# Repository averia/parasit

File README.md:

# % parasit
16 digit for 7 segment display

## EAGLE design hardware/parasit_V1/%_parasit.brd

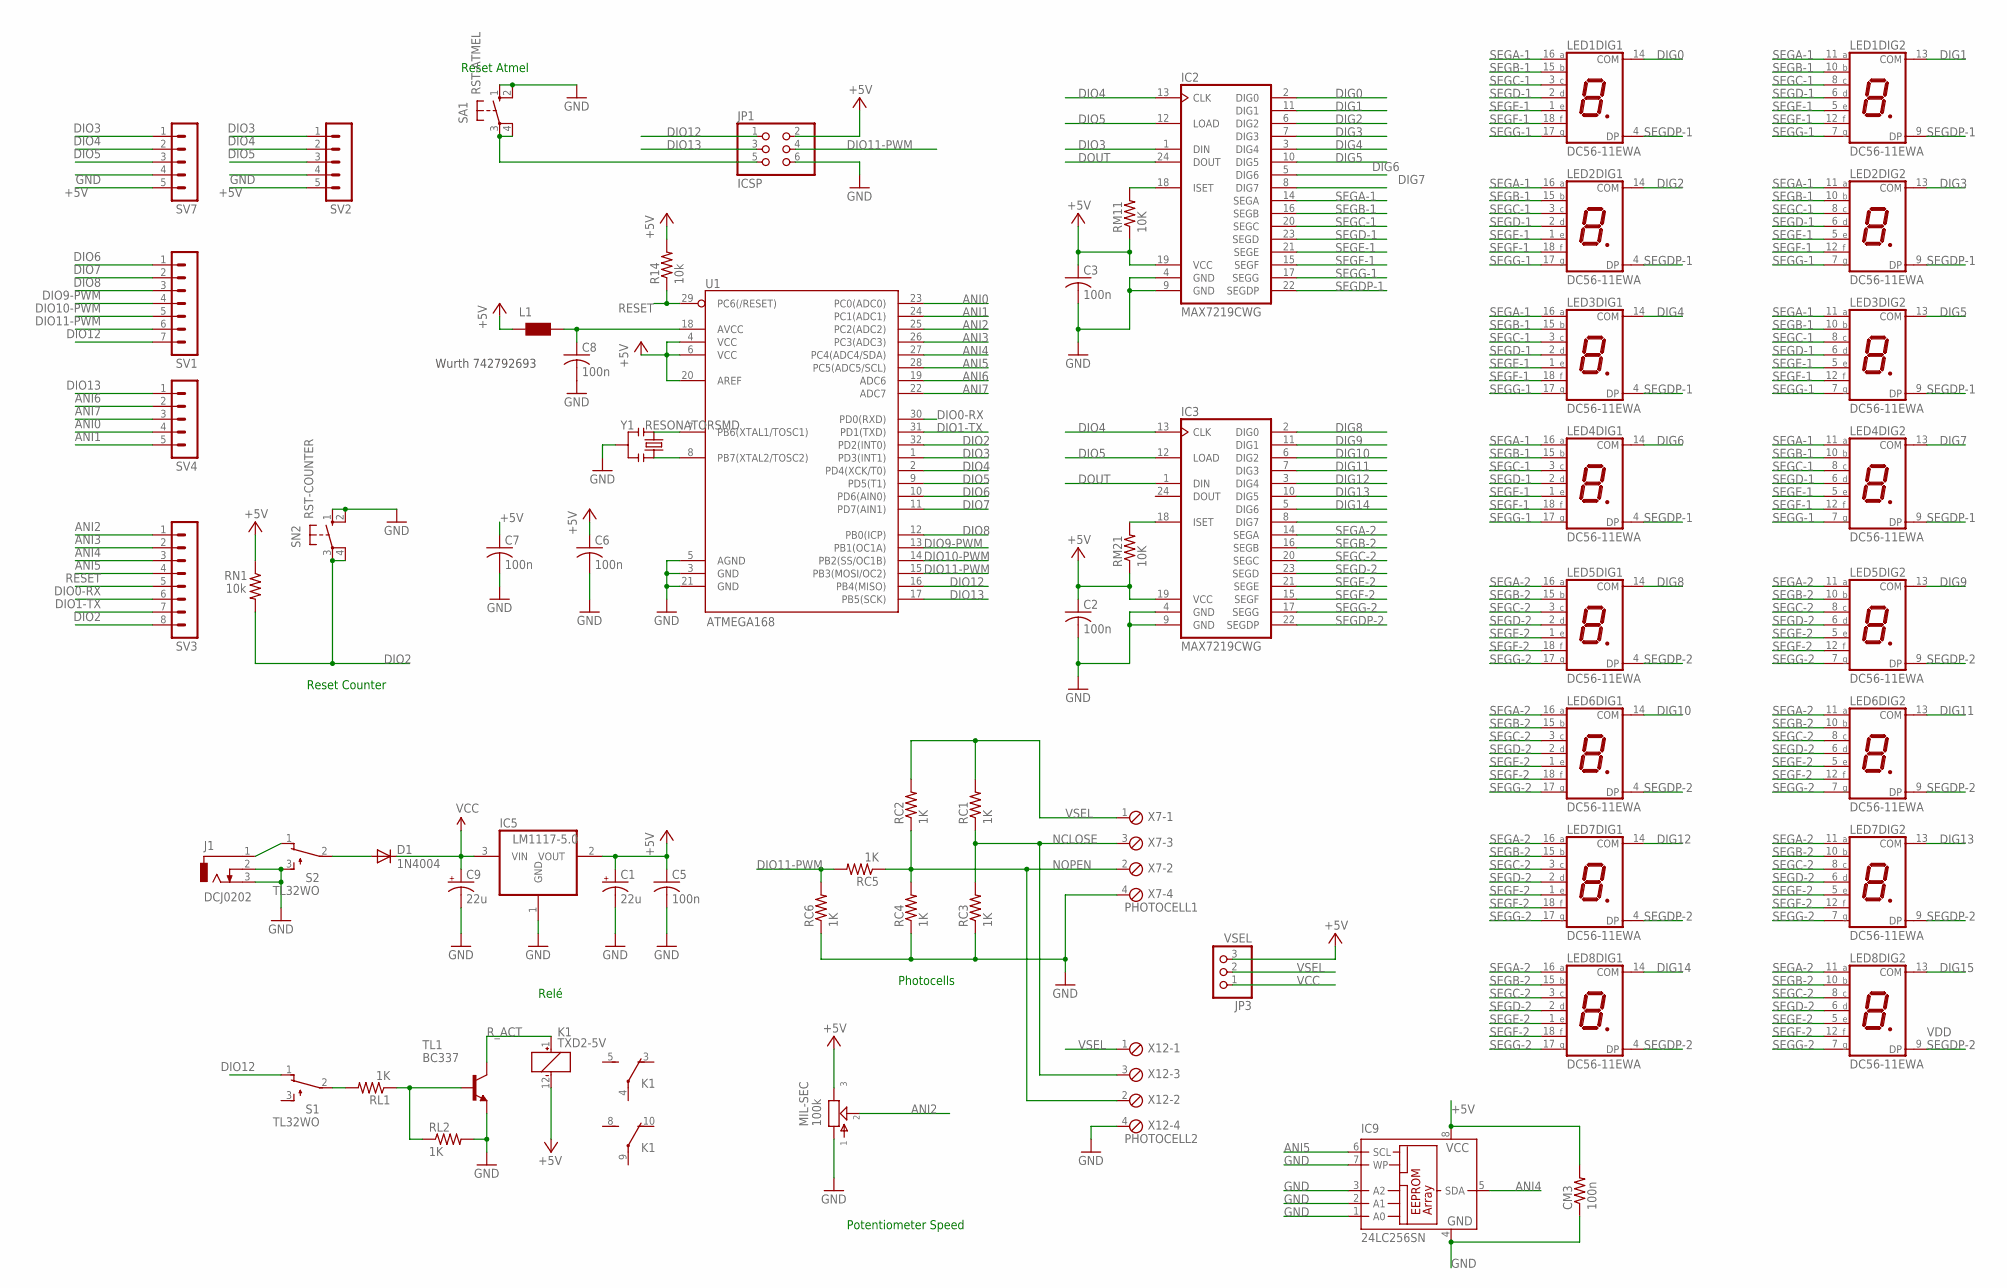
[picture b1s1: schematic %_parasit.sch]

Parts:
C1, C9: 22u; PANASONIC_C
C2, C3, C5, C6, C7, C8: 100n; C0603
CM3: 100n; R0603
D1: 1N4004; DO41-10
IC2, IC3: MAX7219CWG; SO24W
IC5: LM1117-5.0; SOT223
IC9: 24LC256SN; SO-08
J1: DCJ0202
JP1: ICSP; 2X03
JP3: VSEL; 1X03
K1: TXD2-5V; TXD2
L1: WE-CBF_0603; 0603
LED1, LED2, LED3, LED4, LED5, LED6, LED7, LED8: DC56-11EWA; DA56
MIL-SEC: 100k; 16MM-PCB-BRACKETS@1
R14: 10k; R0603
RC1, RC2, RC3, RC4, RC5, RC6: 1K; R0603
RL1, RL2: 1K; R0603
RM11, RM21: 10K; R0603
RN1: 10k; R0603
S1, S2: TL32WO; TL3XWO
SA1: RST-ATMEL; B3F-10XX
SN2: RST-COUNTER; B3F-10XX
SV1: MA07-1
SV2, SV4, SV7: MA05-1
SV3: MA08-1
TL1: BC337; TO92
U1: ATMEGA168; TQFP32-08
X7: PHOTOCELL1; 4POL254
X12: PHOTOCELL2; 4POL254
Y1: RESONATORSMD; RESONATOR-SMD

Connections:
+5V: C1.+, C2.1, C3.1, C5.1, C6.1, C7.1, CM3.2, IC2.19 (VCC), IC3.19 (VCC), IC5.2 (VOUT), IC9.8 (VCC), JP1.2, JP3.3, K1.12 (-), L1.1, MIL-SEC.3, R14.2, RM11.1, RM21.1, RN1.1, SV2.5, SV7.5, U1.4 (VCC), U1.6 (VCC), U1.20 (AREF)
ANI0: SV4.4, U1.23 (PC0(ADC0))
ANI1: SV4.5, U1.24 (PC1(ADC1))
ANI2: MIL-SEC.2, SV3.1, U1.25 (PC2(ADC2))
ANI3: SV3.2, U1.26 (PC3(ADC3))
ANI4: IC9.5 (SDA), SV3.3, U1.27 (PC4(ADC4/SDA))
ANI5: IC9.6 (SCL), SV3.4, U1.28 (PC5(ADC5/SCL))
ANI6: SV4.2, U1.19 (ADC6)
ANI7: SV4.3, U1.22 (ADC7)
DIG0: IC2.2 (DIG0), LED1.14 (COM)
DIG1: IC2.11 (DIG1), LED1.13 (COM)
DIG2: IC2.6 (DIG2), LED2.14 (COM)
DIG3: IC2.7 (DIG3), LED2.13 (COM)
DIG4: IC2.3 (DIG4), LED3.14 (COM)
DIG5: IC2.10 (DIG5), LED3.13 (COM)
DIG6: IC2.5 (DIG6), LED4.14 (COM)
DIG7: IC2.8 (DIG7), LED4.13 (COM)
DIG8: IC3.2 (DIG0), LED5.14 (COM)
DIG9: IC3.11 (DIG1), LED5.13 (COM)
DIG10: IC3.6 (DIG2), LED6.14 (COM)
DIG11: IC3.7 (DIG3), LED6.13 (COM)
DIG12: IC3.3 (DIG4), LED7.14 (COM)
DIG13: IC3.10 (DIG5), LED7.13 (COM)
DIG14: IC3.5 (DIG6), LED8.14 (COM)
DIG15: IC3.8 (DIG7), LED8.13 (COM)
DIO0-RX: SV3.6, U1.30 (PD0(RXD))
DIO1-TX: SV3.7, U1.31 (PD1(TXD))
DIO2: RN1.2, SN2.3, SN2.4 (P1), SV3.8, U1.32 (PD2(INT0))
DIO3: IC2.1 (DIN), SV2.1, SV7.1, U1.1 (PD3(INT1))
DIO4: IC2.13 (CLK), IC3.13 (CLK), SV2.2, SV7.2, U1.2 (PD4(XCK/T0))
DIO5: IC2.12 (LOAD), IC3.12 (LOAD), SV2.3, SV7.3, U1.9 (PD5(T1))
DIO6: SV1.1, U1.10 (PD6(AIN0))
DIO7: SV1.2, U1.11 (PD7(AIN1))
DIO8: SV1.3, U1.12 (PB0(ICP))
DIO9-PWM: SV1.4, U1.13 (PB1(OC1A))
DIO10-PWM: SV1.5, U1.14 (PB2(SS/OC1B))
DIO11-PWM: JP1.4, RC5.2, RC6.2, SV1.6, U1.15 (PB3(MOSI/OC2))
DIO12: JP1.1, S1.1 (O), SV1.7, U1.16 (PB4(MISO))
DIO13: JP1.3, SV4.1, U1.17 (PB5(SCK))
DOUT: IC2.24 (DOUT), IC3.1 (DIN)
GND: C1.-, C2.2, C3.2, C5.2, C6.2, C7.2, C8.2, C9.-, CM3.1, IC2.4 (GND), IC2.9 (GND), IC3.4 (GND), IC3.9 (GND), IC5.1 (GND), IC9.1 (A0), IC9.2 (A1), IC9.3 (A2), IC9.4 (GND), IC9.7 (WP), J1.2, J1.3, JP1.6, MIL-SEC.1, RC3.1, RC4.1, RC6.1, RL2.2, S2.3 (S), SA1.1 (S), SA1.2 (S1), SN2.1 (S), SN2.2 (S1), SV2.4, SV7.4, TL1.1 (E), U1.3 (GND), U1.5 (AGND), U1.21 (GND), X7.4, X12.4, Y1.2
unnamed: J1.1, S2.1 (O)
unnamed: D1.A, S2.2
unnamed: RL1.2, S1.2
unnamed: RL1.1, RL2.1, TL1.2 (B)
unnamed: U1.7 (PB6(XTAL1/TOSC1)), Y1.1
unnamed: IC2.18 (ISET), RM11.2
unnamed: IC3.18 (ISET), RM21.2
unnamed: U1.8 (PB7(XTAL2/TOSC2)), Y1.3
unnamed: C8.1, L1.2, U1.18 (AVCC)
NCLOSE: RC1.1, RC3.2, X7.3, X12.3
NOPEN: RC2.1, RC4.2, RC5.1, X7.2, X12.2
RESET: JP1.5, R14.1, SA1.3, SA1.4 (P1), SV3.5, U1.29 (PC6(/RESET))
R_ACT: K1.1 (+), TL1.3 (C)
SEGA-1: IC2.14 (SEGA), LED1.11 (A), LED1.16 (A), LED2.11 (A), LED2.16 (A), LED3.11 (A), LED3.16 (A), LED4.11 (A), LED4.16 (A)
SEGA-2: IC3.14 (SEGA), LED5.11 (A), LED5.16 (A), LED6.11 (A), LED6.16 (A), LED7.11 (A), LED7.16 (A), LED8.11 (A), LED8.16 (A)
SEGB-1: IC2.16 (SEGB), LED1.10 (B), LED1.15 (B), LED2.10 (B), LED2.15 (B), LED3.10 (B), LED3.15 (B), LED4.10 (B), LED4.15 (B)
SEGB-2: IC3.16 (SEGB), LED5.10 (B), LED5.15 (B), LED6.10 (B), LED6.15 (B), LED7.10 (B), LED7.15 (B), LED8.10 (B), LED8.15 (B)
SEGC-1: IC2.20 (SEGC), LED1.3 (C), LED1.8 (C), LED2.3 (C), LED2.8 (C), LED3.3 (C), LED3.8 (C), LED4.3 (C), LED4.8 (C)
SEGC-2: IC3.20 (SEGC), LED5.3 (C), LED5.8 (C), LED6.3 (C), LED6.8 (C), LED7.3 (C), LED7.8 (C), LED8.3 (C), LED8.8 (C)
SEGD-1: IC2.23 (SEGD), LED1.2 (D), LED1.6 (D), LED2.2 (D), LED2.6 (D), LED3.2 (D), LED3.6 (D), LED4.2 (D), LED4.6 (D)
SEGD-2: IC3.23 (SEGD), LED5.2 (D), LED5.6 (D), LED6.2 (D), LED6.6 (D), LED7.2 (D), LED7.6 (D), LED8.2 (D), LED8.6 (D)
SEGDP-1: IC2.22 (SEGDP), LED1.4 (DP), LED1.9 (DP), LED2.4 (DP), LED2.9 (DP), LED3.4 (DP), LED3.9 (DP), LED4.4 (DP), LED4.9 (DP)
SEGDP-2: IC3.22 (SEGDP), LED5.4 (DP), LED5.9 (DP), LED6.4 (DP), LED6.9 (DP), LED7.4 (DP), LED7.9 (DP), LED8.4 (DP), LED8.9 (DP)
SEGE-1: IC2.21 (SEGE), LED1.1 (E), LED1.5 (E), LED2.1 (E), LED2.5 (E), LED3.1 (E), LED3.5 (E), LED4.1 (E), LED4.5 (E)
SEGE-2: IC3.21 (SEGE), LED5.1 (E), LED5.5 (E), LED6.1 (E), LED6.5 (E), LED7.1 (E), LED7.5 (E), LED8.1 (E), LED8.5 (E)
SEGF-1: IC2.15 (SEGF), LED1.12 (F), LED1.18 (F), LED2.12 (F), LED2.18 (F), LED3.12 (F), LED3.18 (F), LED4.12 (F), LED4.18 (F)
SEGF-2: IC3.15 (SEGF), LED5.12 (F), LED5.18 (F), LED6.12 (F), LED6.18 (F), LED7.12 (F), LED7.18 (F), LED8.12 (F), LED8.18 (F)
SEGG-1: IC2.17 (SEGG), LED1.7 (G), LED1.17 (G), LED2.7 (G), LED2.17 (G), LED3.7 (G), LED3.17 (G), LED4.7 (G), LED4.17 (G)
SEGG-2: IC3.17 (SEGG), LED5.7 (G), LED5.17 (G), LED6.7 (G), LED6.17 (G), LED7.7 (G), LED7.17 (G), LED8.7 (G), LED8.17 (G)
VCC: C9.+, D1.C, IC5.3 (VIN), JP3.1
VSEL: JP3.2, RC1.2, RC2.2, X7.1, X12.1

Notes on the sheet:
Reset Counter
Reset Atmel
Photocells
Relé
Wurth 742792693
Potentiometer Speed

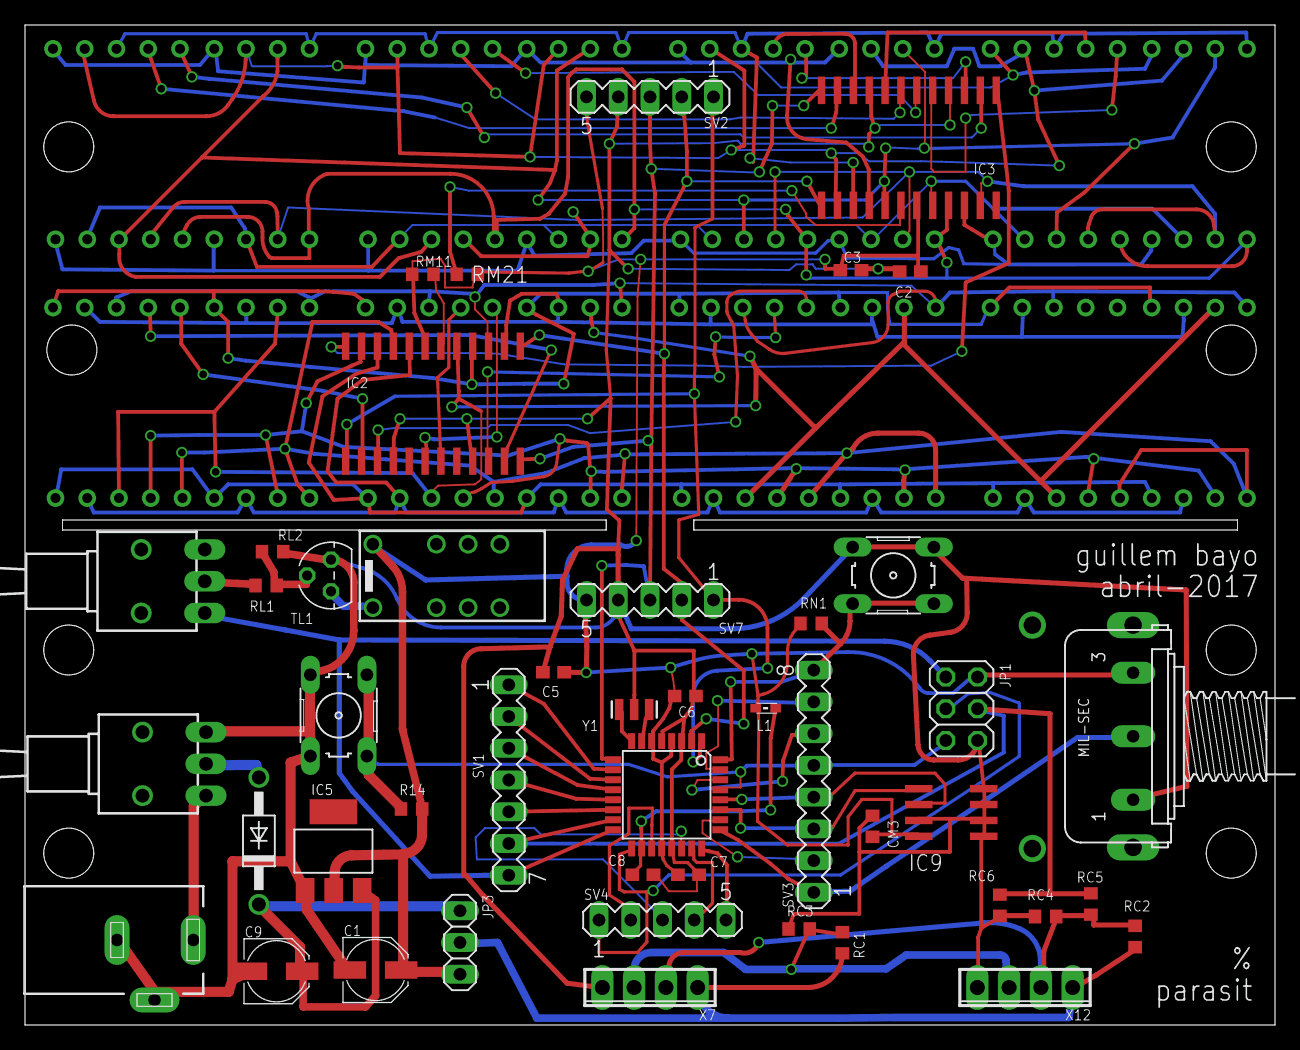
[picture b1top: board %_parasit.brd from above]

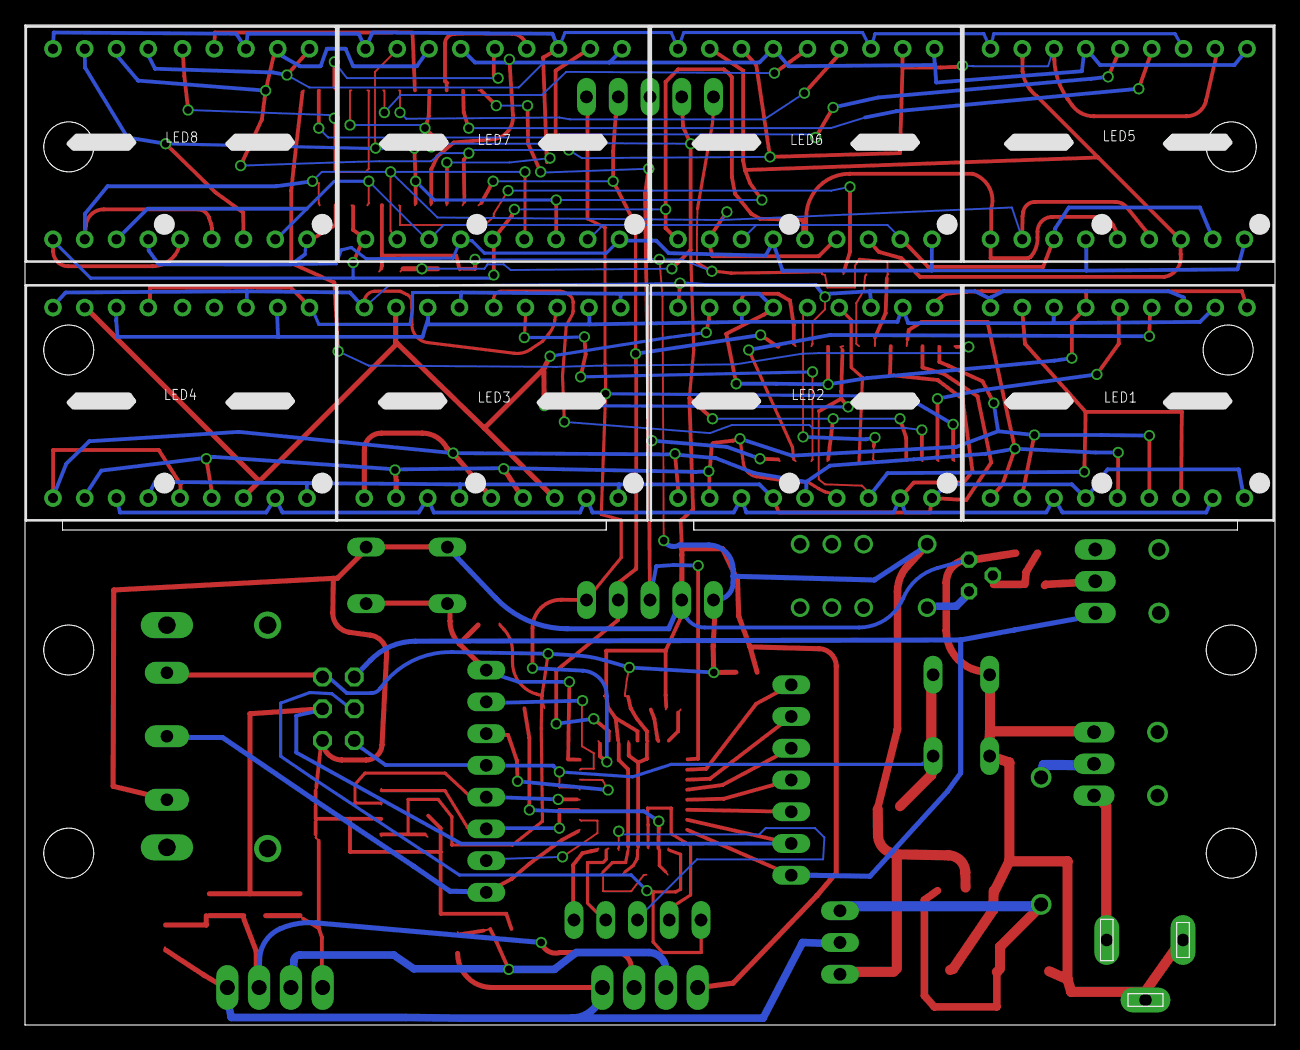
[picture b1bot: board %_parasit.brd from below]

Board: 2 copper layers, 100.0 x 80.0 mm, 54 parts (8 on the bottom side), 72 nets.
